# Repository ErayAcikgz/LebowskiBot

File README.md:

# LebowskiBot
6 DOF Robot with speed control, path planning and AI-assisted image processing.

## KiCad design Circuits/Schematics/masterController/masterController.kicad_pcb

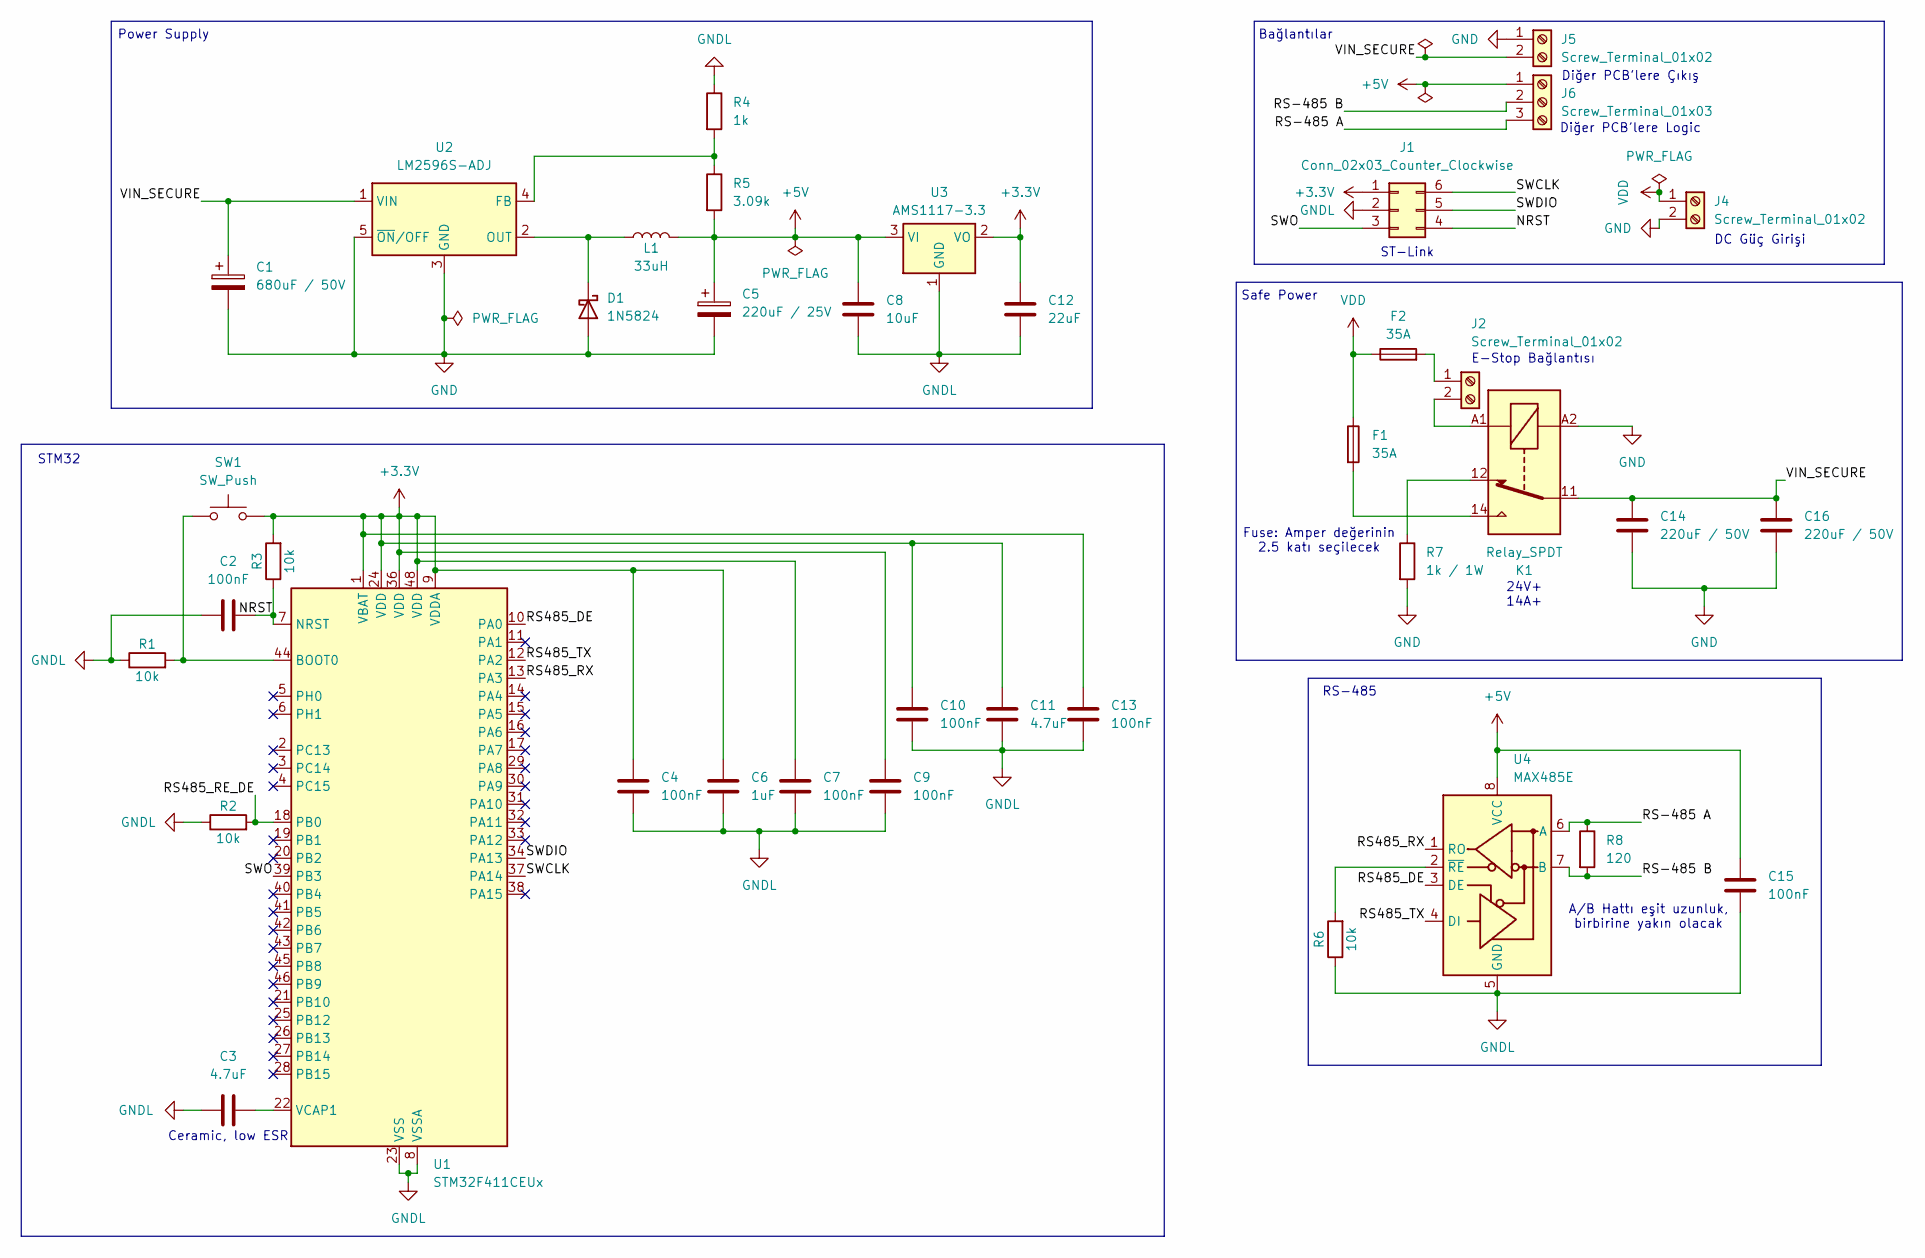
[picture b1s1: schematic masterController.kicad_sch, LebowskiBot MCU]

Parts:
C1: 680uF / 50V; C_Radial_D12.5mm_H25.0mm_P5.00mm
C2, C4, C7, C9, C10, C13, C15: 100nF; C_0805_2012Metric_Pad1.18x1.45mm_HandSolder
C3, C11: 4.7uF; C_Elec_5x5.4
C5: 220uF / 25V; C_Elec_10x10.2
C6: 1uF; C_0805_2012Metric_Pad1.18x1.45mm_HandSolder
C8: 10uF; C_Elec_6.3x5.8
C12: 22uF; C_Elec_6.3x5.4
C14, C16: 220uF / 50V; CP_Radial_D10.0mm_P5.00mm
D1: 1N5824; D_SMC_Handsoldering
F1, F2: 35A; HT-01-A
J1: Conn_02x03_Counter_Clockwise; PinHeader_2x03_P2.54mm_Vertical
J2, J4, J5: Screw_Terminal_01x02; TerminalBlock_Phoenix_PT-1,5-2-5.0-H_1x02_P5.00mm_Horizontal
J6: Screw_Terminal_01x03; TerminalBlock_Phoenix_PT-1,5-3-5.0-H_1x03_P5.00mm_Horizontal
K1: Relay_SPDT; Relay_SPDT_Finder_40.61
L1: 33uH; L_12x12mm_H8mm
R1, R2, R3, R6: 10k; R_0805_2012Metric_Pad1.20x1.40mm_HandSolder
R4: 1k; R_0805_2012Metric_Pad1.20x1.40mm_HandSolder
R5: 3.09k; R_0805_2012Metric_Pad1.20x1.40mm_HandSolder
R7: 1k / 1W; R_2512_6332Metric
R8: 120; R_0805_2012Metric_Pad1.20x1.40mm_HandSolder
SW1: SW_Push; SW_PUSH_6mm_H4.3mm
U1: STM32F411CEUx; QFN-48-1EP_7x7mm_P0.5mm_EP5.6x5.6mm
U2: LM2596S-ADJ; TO-263-5_TabPin3
U3: AMS1117-3.3; SOT-223-3_TabPin2
U4: MAX485E; SOIC-8_3.9x4.9mm_P1.27mm

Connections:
+3.3V: C4.2, C6.2, C7.2, C9.2, C10.2, C11.2, C12.1, C13.2, J1.1, R3.2, SW1.2, U1.1 (VBAT), U1.9 (VDDA), U1.24 (VDD), U1.36 (VDD), U1.48 (VDD), U3.2 (VO)
+5V: C5.1, C8.1, C15.1, J6.1, L1.2, R5.2, U3.3 (VI), U4.8 (VCC)
/NRST: C2.2, J1.4, R3.1, U1.7 (NRST)
/RS485_DE: U1.10 (PA0), U4.3 (DE)
/RS485_RE_DE: R2.2, U1.18 (PB0)
/RS485_RX: U1.13 (PA3), U4.1 (RO)
/RS485_TX: U1.12 (PA2), U4.4 (DI)
/RS-485 A: J6.3, R8.1, U4.6 (A)
/RS-485 B: J6.2, R8.2, U4.7 (B)
/SWCLK: J1.6, U1.37 (PA14)
/SWDIO: J1.5, U1.34 (PA13)
/SWO: J1.3, U1.39 (PB3)
/VIN_SECURE: C1.1, C14.1, C16.1, J5.2, K1.11, U2.1 (VIN)
GND: C1.2, C5.2, C14.2, C16.2, D1.2 (A), J4.2, J5.1, K1.A2, R7.2, U2.3 (GND), U2.5 (~ON/OFF)
GNDL: C2.1, C3.1, C4.1, C6.1, C7.1, C8.2, C9.1, C10.1, C11.1, C12.2, C13.1, C15.2, J1.2, R1.1, R2.1, R4.1, R6.1, U1.8 (VSSA), U1.23 (VSS), U1.35 (VSS), U1.47 (VSS), U1.49 (VSS), U3.1 (GND), U4.5 (GND)
unnamed: D1.1 (K), L1.1, U2.2 (OUT)
unnamed: F1.2, K1.14
unnamed: F2.2, J2.1
unnamed: J2.2, K1.A1
unnamed: K1.12, R7.1
unnamed: R1.2, SW1.1, U1.44 (BOOT0)
unnamed: C3.2, U1.22 (VCAP1)
unnamed: R4.2, R5.1, U2.4 (FB)
unnamed: R6.2, U4.2 (~RE)
VDD: F1.1, F2.1, J4.1

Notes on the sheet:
Bağlantılar
DC Güç Girişi
STM32
Diğer PCB'lere Çıkış
RS-485
Diğer PCB'lere Logic
Ceramic, low ESR
Fuse: Amper değerinin 2.5 katı seçilecek
24V+ 14A+
A/B Hattı eşit uzunluk, birbirine yakın olacak
Safe Power
Power Supply
E-Stop Bağlantısı
ST-Link

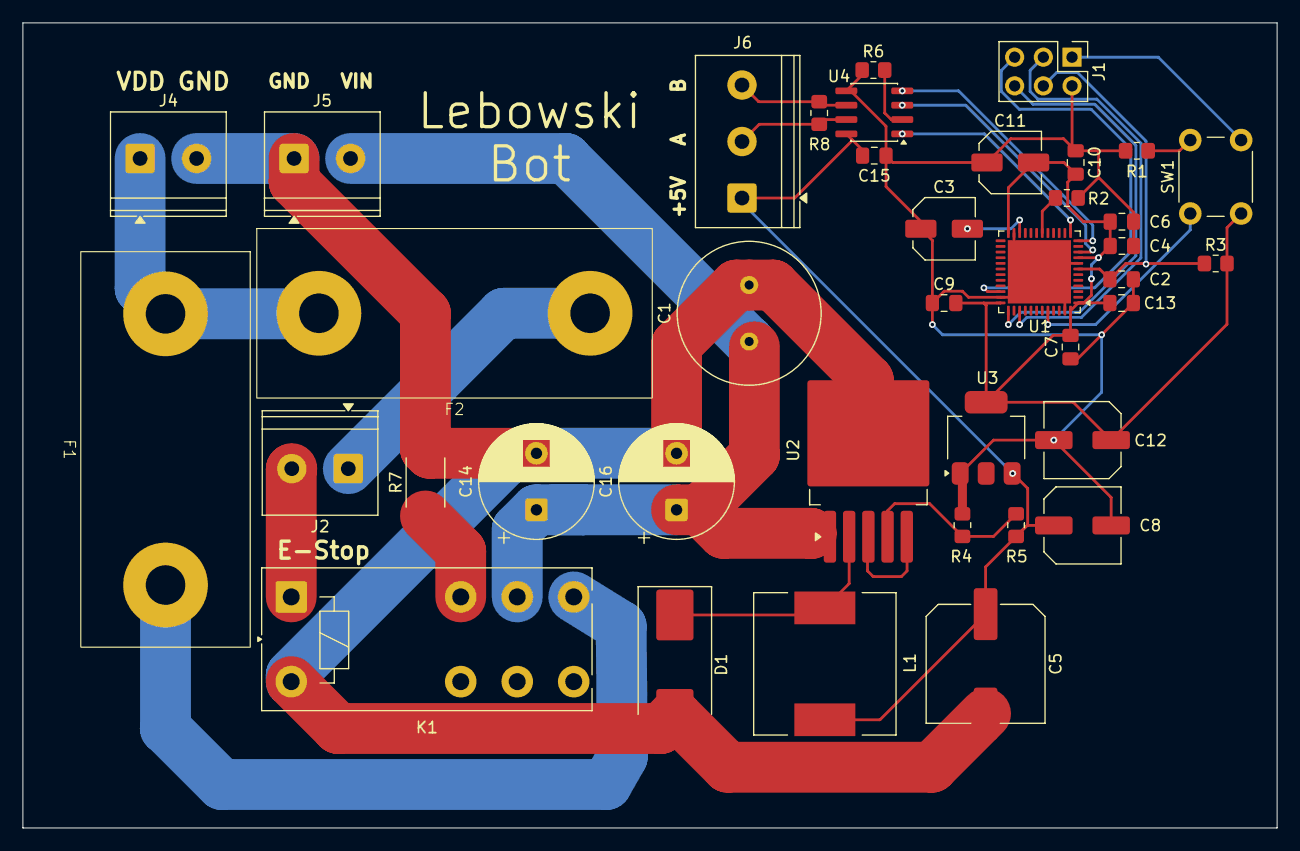
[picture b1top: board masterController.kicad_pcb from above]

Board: 2 copper layers, 111.0 x 71.2 mm, 39 parts (0 on the bottom side), 25 nets.

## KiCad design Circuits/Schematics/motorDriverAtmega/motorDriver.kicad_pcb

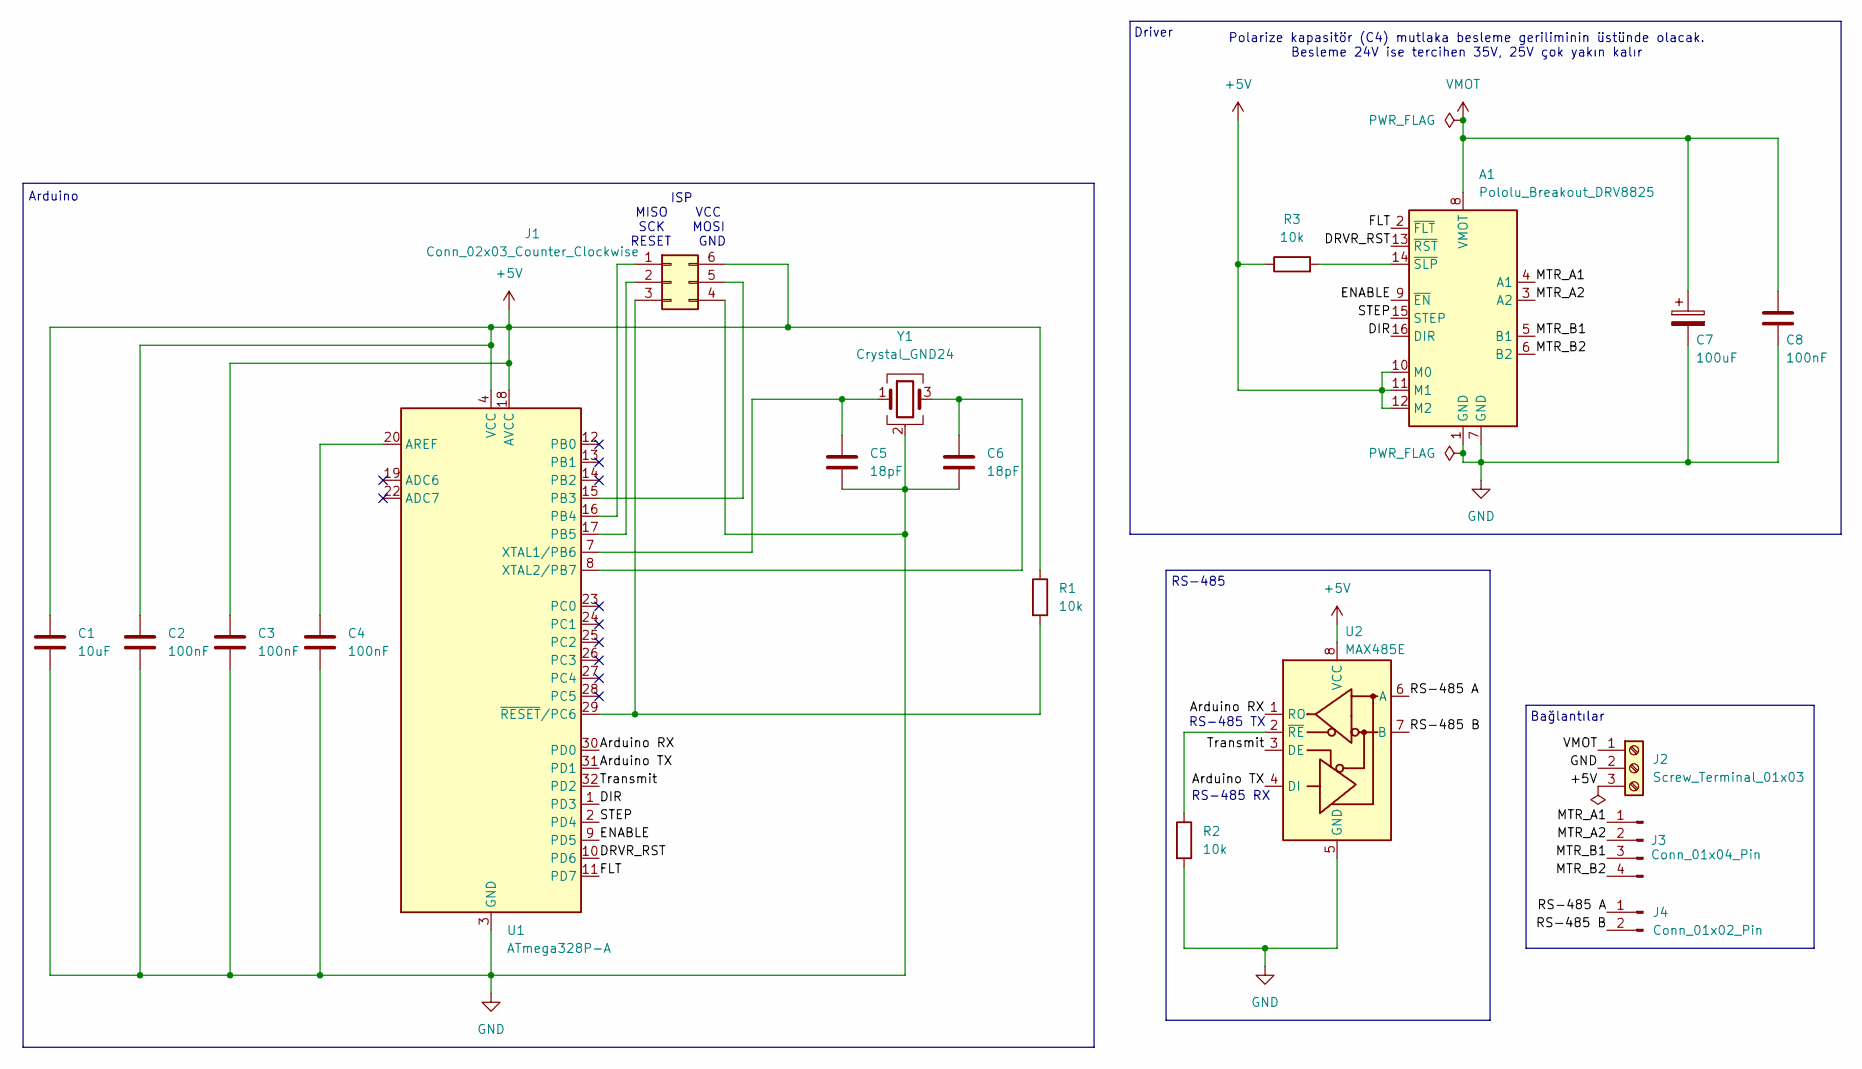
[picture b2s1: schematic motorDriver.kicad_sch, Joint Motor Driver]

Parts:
A1: Pololu_Breakout_DRV8825; Pololu_Breakout-16_15.2x20.3mm
C1: 10uF; C_0805_2012Metric_Pad1.18x1.45mm_HandSolder
C2, C3, C4, C8: 100nF; C_0805_2012Metric_Pad1.18x1.45mm_HandSolder
C5, C6: 18pF; C_0805_2012Metric_Pad1.18x1.45mm_HandSolder
C7: 100uF; CP_Elec_6.3x5.3
J1: Conn_02x03_Counter_Clockwise; PinHeader_2x03_P2.54mm_Vertical
J2: Screw_Terminal_01x03; TerminalBlock_Phoenix_PT-1,5-3-5.0-H_1x03_P5.00mm_Horizontal
J3: Conn_01x04_Pin; PinHeader_1x04_P2.54mm_Vertical
J4: Conn_01x02_Pin; PinHeader_1x02_P2.54mm_Vertical
R1, R2, R3: 10k; R_0805_2012Metric_Pad1.20x1.40mm_HandSolder
U1: ATmega328P-A; TQFP-32_7x7mm_P0.8mm
U2: MAX485E; SOIC-8_3.9x4.9mm_P1.27mm
Y1: Crystal_GND24; Crystal_SMD_3225-4Pin_3.2x2.5mm

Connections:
+5V: A1.10 (M0), A1.11 (M1), A1.12 (M2), C1.1, C2.1, C3.1, J1.6, J2.3, R1.1, R3.1, U1.4 (VCC), U1.6 (VCC), U1.18 (AVCC), U2.8 (VCC)
/Arduino RX: U1.30 (PD0), U2.1 (RO)
/Arduino TX: U1.31 (PD1), U2.4 (DI)
/DIR: A1.16 (DIR), U1.1 (PD3)
/DRVR_RST: A1.13 (~RST), U1.10 (PD6)
/ENABLE: A1.9 (~EN), U1.9 (PD5)
/FLT: A1.2 (~FLT), U1.11 (PD7)
/MTR_A1: A1.4 (A1), J3.1
/MTR_A2: A1.3 (A2), J3.2
/MTR_B1: A1.5 (B1), J3.3
/MTR_B2: A1.6 (B2), J3.4
/RS-485 A: J4.1, U2.6 (A)
/RS-485 B: J4.2, U2.7 (B)
/STEP: A1.15 (STEP), U1.2 (PD4)
/Transmit: U1.32 (PD2), U2.3 (DE)
GND: A1.1 (GND), A1.7 (GND), C1.2, C2.2, C3.2, C4.2, C5.2, C6.2, C7.2, C8.2, J1.4, J2.2, R2.2, U1.3 (GND), U1.5 (GND), U1.21 (GND), U2.5 (GND), Y1.2 (G), Y1.4 (G)
unnamed: A1.14 (~SLP), R3.2
unnamed: J1.1, U1.16 (PB4)
unnamed: J1.2, U1.17 (PB5)
unnamed: J1.3, R1.2, U1.29 (~RESET/PC6)
unnamed: J1.5, U1.15 (PB3)
unnamed: C4.1, U1.20 (AREF)
unnamed: C5.1, U1.7 (XTAL1/PB6), Y1.1
unnamed: C6.1, U1.8 (XTAL2/PB7), Y1.3
unnamed: R2.1, U2.2 (~RE)
VMOT: A1.8 (VMOT), C7.1, C8.1, J2.1

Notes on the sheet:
RS-485
Driver
Polarize kapasitör (C4) mutlaka besleme geriliminin üstünde olacak. Besleme 24V ise tercihen 35V, 25V çok yakın kalır
Bağlantılar
RS-485 RX
Arduino
ISP MISO VCC SCK MOSI RESET GND
RS-485 TX

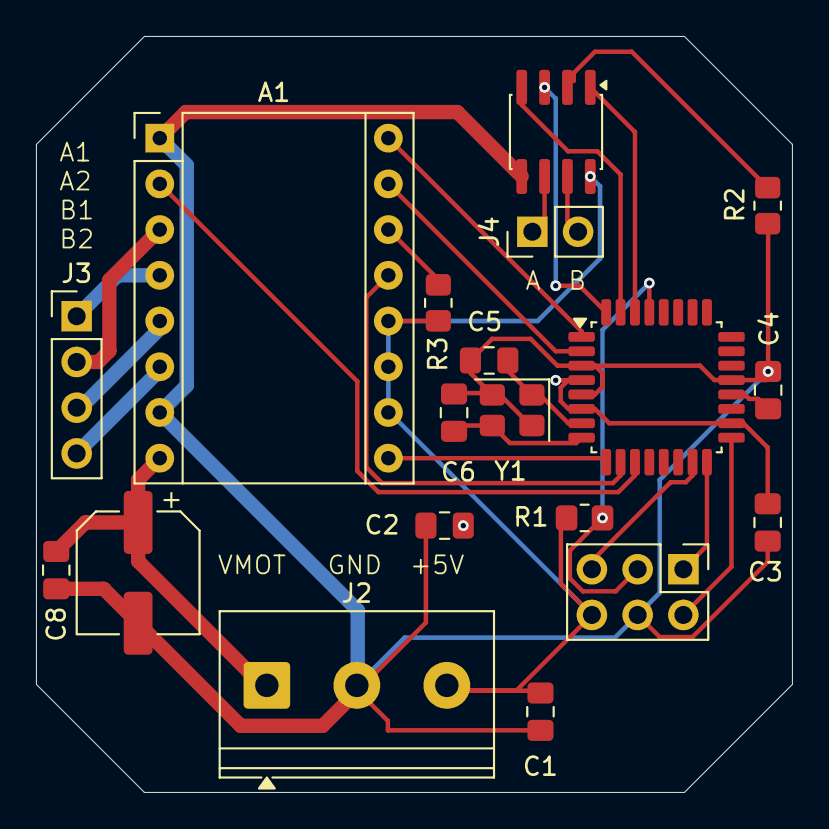
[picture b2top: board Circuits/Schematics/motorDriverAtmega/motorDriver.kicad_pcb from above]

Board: 2 copper layers, 42.0 x 42.0 mm, 19 parts (0 on the bottom side), 26 nets.

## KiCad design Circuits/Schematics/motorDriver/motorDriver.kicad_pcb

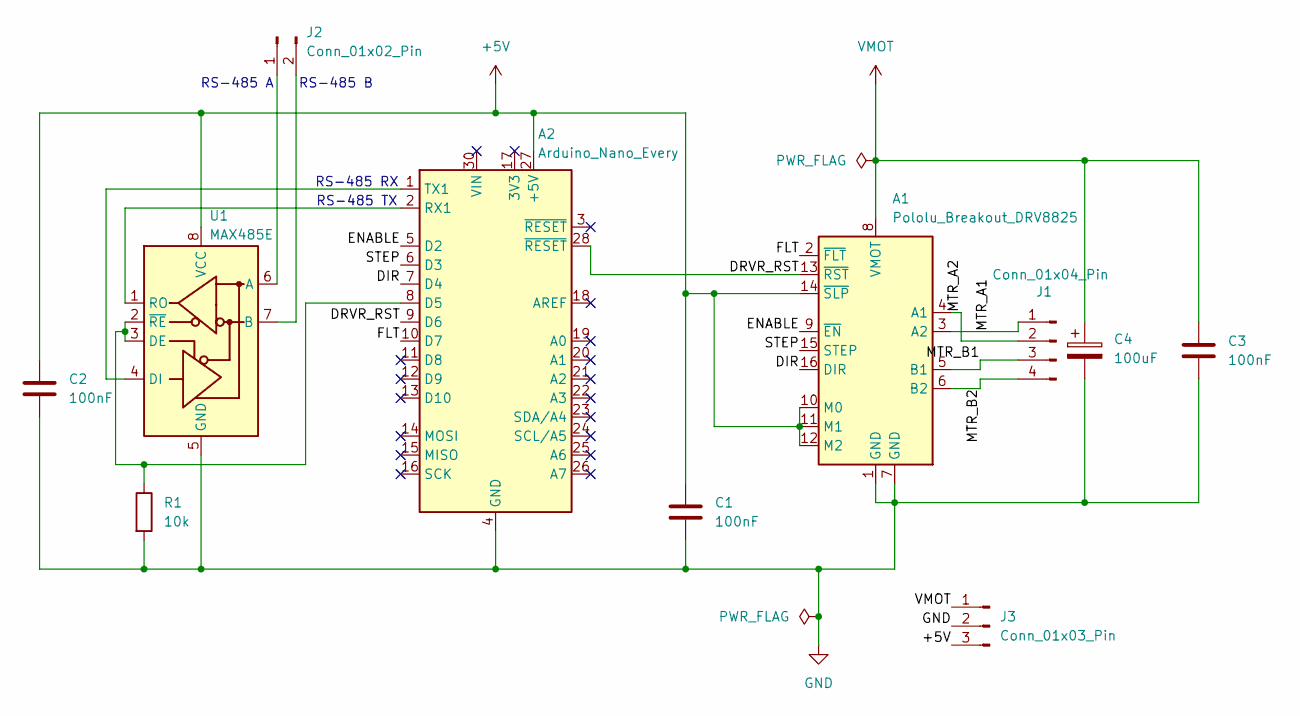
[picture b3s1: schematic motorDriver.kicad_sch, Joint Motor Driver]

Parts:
A1: Pololu_Breakout_DRV8825; Pololu_Breakout-16_15.2x20.3mm
A2: Arduino_Nano_Every; Arduino_Nano
C1, C2, C3: 100nF; C_0805_2012Metric_Pad1.18x1.45mm_HandSolder
C4: 100uF; CP_Elec_6.3x5.3
J1: Conn_01x04_Pin; PinHeader_1x04_P2.54mm_Vertical
J2: Conn_01x02_Pin; PinHeader_1x02_P2.54mm_Vertical
J3: Conn_01x03_Pin; PinHeader_1x03_P2.54mm_Vertical
R1: 10k; R_0805_2012Metric_Pad1.20x1.40mm_HandSolder
U1: MAX485E; SOIC-8_3.9x4.9mm_P1.27mm

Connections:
+5V: A1.10 (M0), A1.11 (M1), A1.12 (M2), A1.14 (~SLP), A2.27 (+5V), C1.1, C2.1, J3.3, U1.8 (VCC)
/DIR: A1.16 (DIR), A2.7 (D4)
/DRVR_RST: A1.13 (~RST), A2.9 (D6), A2.28 (~RESET)
/ENABLE: A1.9 (~EN), A2.5 (D2)
/FLT: A1.2 (~FLT), A2.10 (D7)
/MTR_A1: A1.3 (A2), J1.1
/MTR_A2: A1.4 (A1), J1.2
/MTR_B1: A1.5 (B1), J1.3
/MTR_B2: A1.6 (B2), J1.4
/STEP: A1.15 (STEP), A2.6 (D3)
GND: A1.1 (GND), A1.7 (GND), A2.4 (GND), A2.29 (GND), C1.2, C2.2, C3.2, C4.2, J3.2, R1.2, U1.5 (GND)
unnamed: A2.8 (D5), R1.1, U1.2 (~RE), U1.3 (DE)
unnamed: A2.2 (RX1), U1.1 (RO)
unnamed: A2.1 (TX1), U1.4 (DI)
unnamed: J2.1, U1.6 (A)
unnamed: J2.2, U1.7 (B)
VMOT: A1.8 (VMOT), C3.1, C4.1, J3.1

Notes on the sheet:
RS-485 RX
RS-485 B
RS-485 TX
RS-485 A

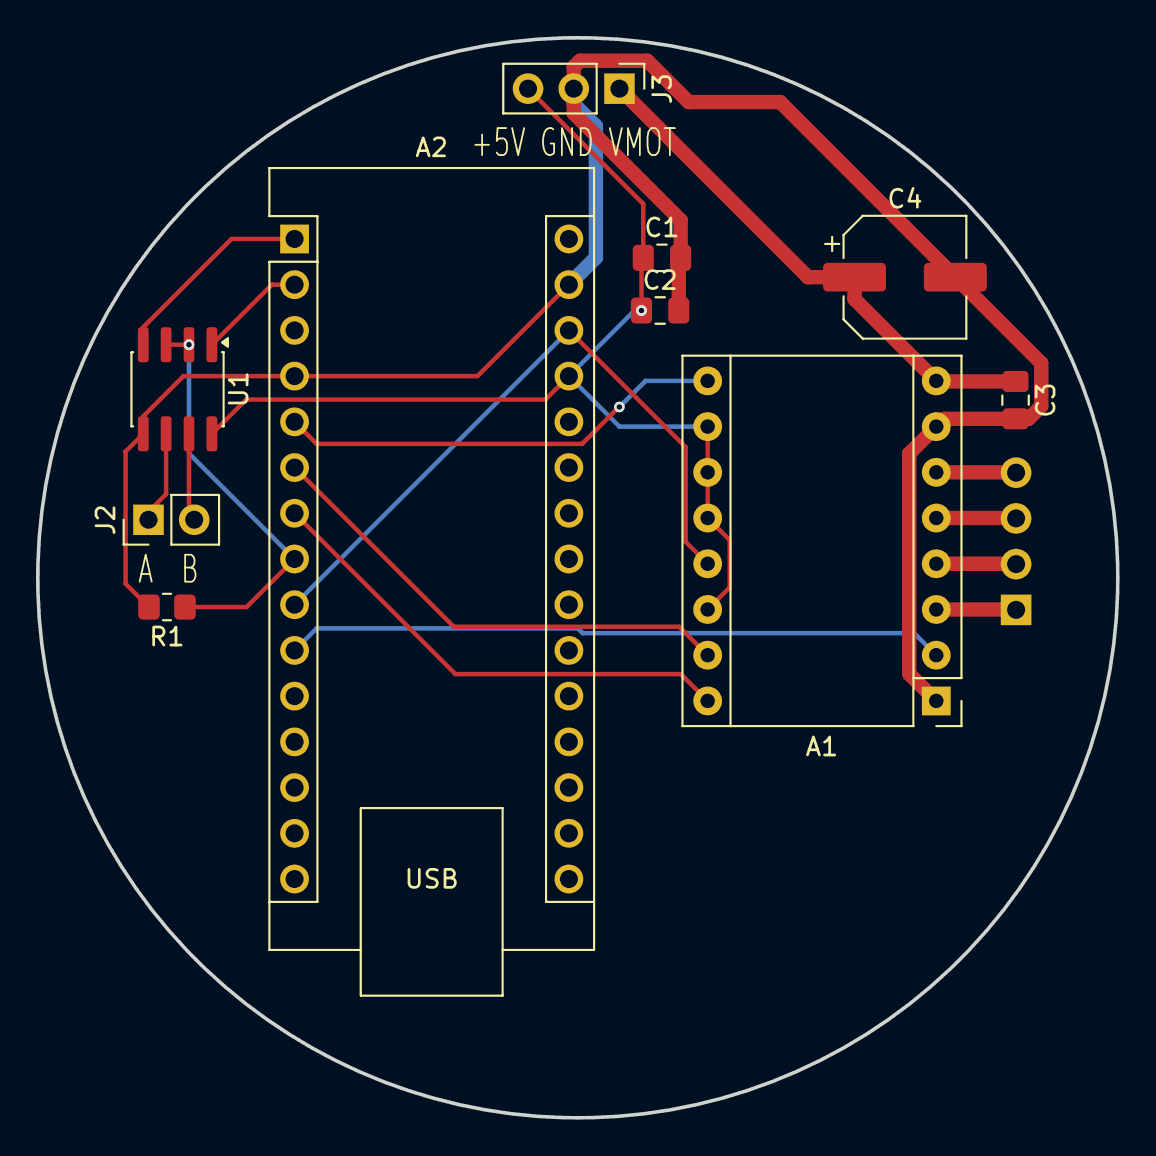
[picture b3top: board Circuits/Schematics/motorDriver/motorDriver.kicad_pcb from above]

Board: 2 copper layers, 60.0 x 60.0 mm, 11 parts (1 on the bottom side), 17 nets.
